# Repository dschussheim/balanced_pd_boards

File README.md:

# balanced_pd_boards
Eagle files for balance photodiode detectors

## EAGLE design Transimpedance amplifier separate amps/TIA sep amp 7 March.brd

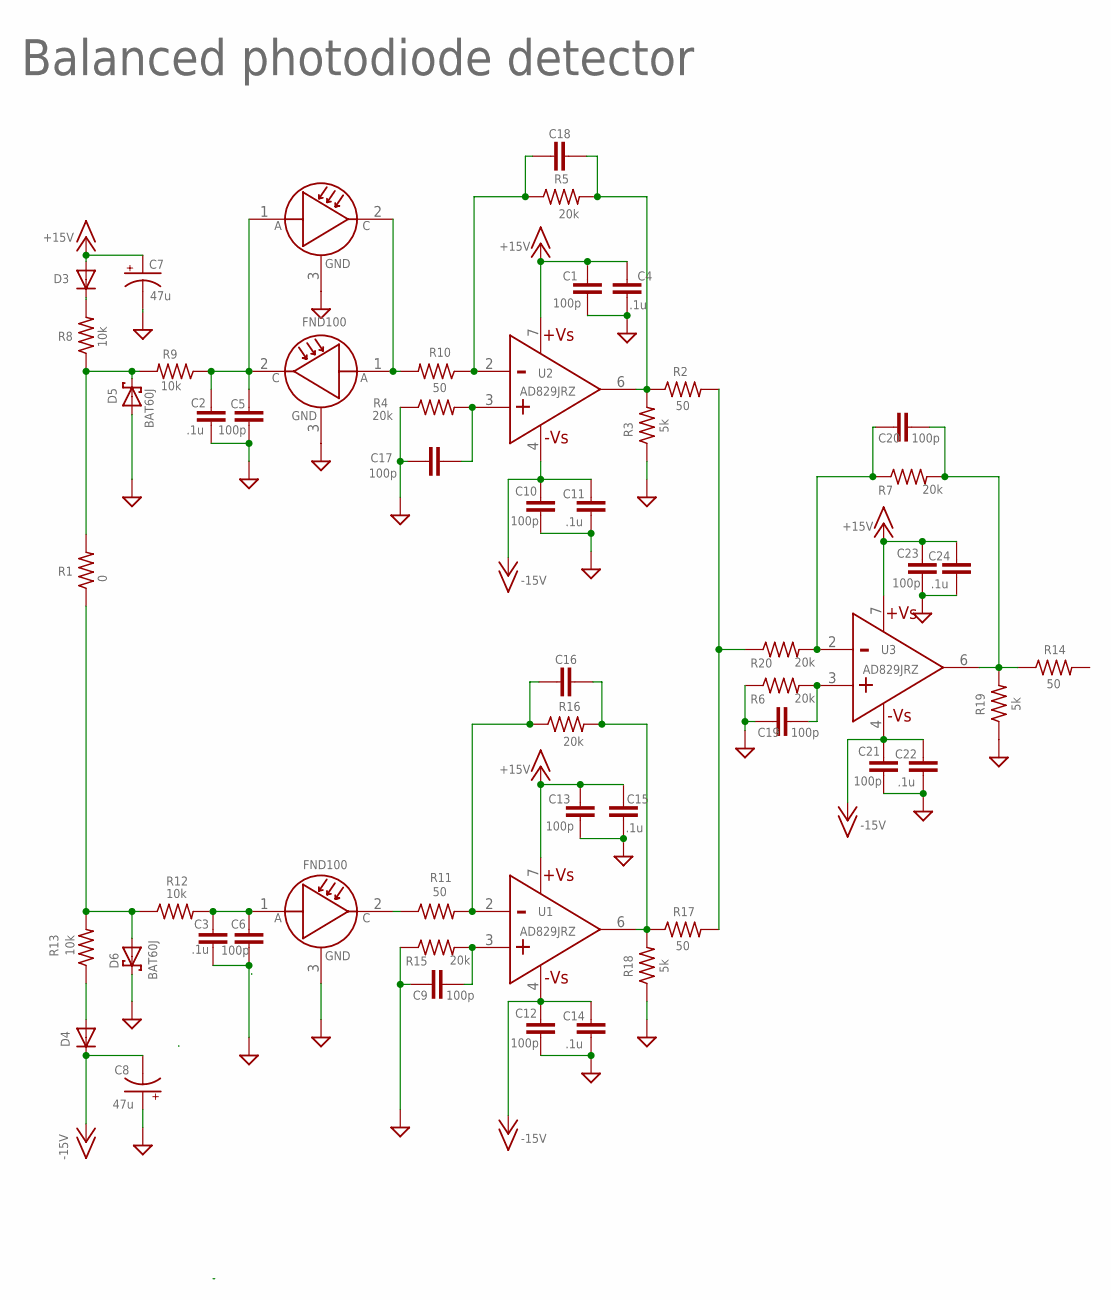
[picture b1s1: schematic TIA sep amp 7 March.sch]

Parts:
C1, C5, C6, C9, C10, C12, C13, C17, C19, C20, C21, C23: 100p; C0603
C2, C3, C4, C11, C14, C15, C22, C24: .1u; C0603
C7, C8: 47u; ETR3
C16, C18: C-EUC0603; C0603
D3, D4: SOD523DIODE; SOD523
D5, D6: BAT60J; SOD323_ST
R1: 0; R0603
R2, R10, R11, R14, R17: 50; R0603
R3, R18, R19: 5k; R0603
R4, R5, R6, R7, R15, R16, R20: 20k; R0603
R8, R9, R12, R13: 10k; R0603
U1, U2, U3: AD829JRZ; SOIC127P600X175-8N
U$1, U$2, U$4: FND100; TO254P939X470-3P

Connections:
+15V: C1.2, C4.2, C7.+, C13.2, C15.2, C23.2, C24.2, D3.A, U1.7 (+VS), U2.7 (+VS), U3.7 (+VS)
-15V: C8.-, C10.2, C11.2, C12.2, C14.2, C21.2, C22.2, D4.C, U1.4 (-VS), U2.4 (-VS), U3.4 (-VS)
GND: C1.1, C2.1, C3.1, C4.1, C5.1, C6.1, C7.-, C8.+, C9.1, C10.1, C11.1, C12.1, C13.1, C14.1, C15.1, C17.1, C19.1, C21.1, C22.1, C23.1, C24.1, D5.A, D6.C, R3.1, R4.1, R6.1, R15.1, R18.1, R19.1, U$1.3 (GND), U$2.3 (GND), U$4.3 (GND)
unnamed: D3.C, R8.2
unnamed: C16.1, R11.2, R16.1, U1.2 (-IN)
unnamed: C16.2, R16.2, R17.1, R18.2, U1.6 (OUTPUT)
unnamed: C17.2, R4.2, U2.3 (+IN)
unnamed: C2.2, C5.2, R9.1, U$1.2 (C), U$4.1 (A)
unnamed: C18.1, R5.1, R10.1, U2.2 (-IN)
unnamed: D5.C, R1.2, R8.1, R9.2
unnamed: R10.2, U$1.1 (A), U$4.2 (C)
unnamed: R11.1, U$2.2 (C)
unnamed: C3.2, C6.2, R12.2, U$2.1 (A)
unnamed: D6.A, R1.1, R12.1, R13.2
unnamed: D4.A, R13.1
unnamed: R2.2, R17.2, R20.1
unnamed: C18.2, R2.1, R3.2, R5.2, U2.6 (OUTPUT)
unnamed: C9.2, R15.2, U1.3 (+IN)
unnamed: C19.2, R6.2, U3.3 (+IN)
unnamed: C20.2, R7.2, R14.1, R19.2, U3.6 (OUTPUT)
unnamed: C20.1, R7.1, R20.2, U3.2 (-IN)

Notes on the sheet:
FND100
Balanced photodiode detector

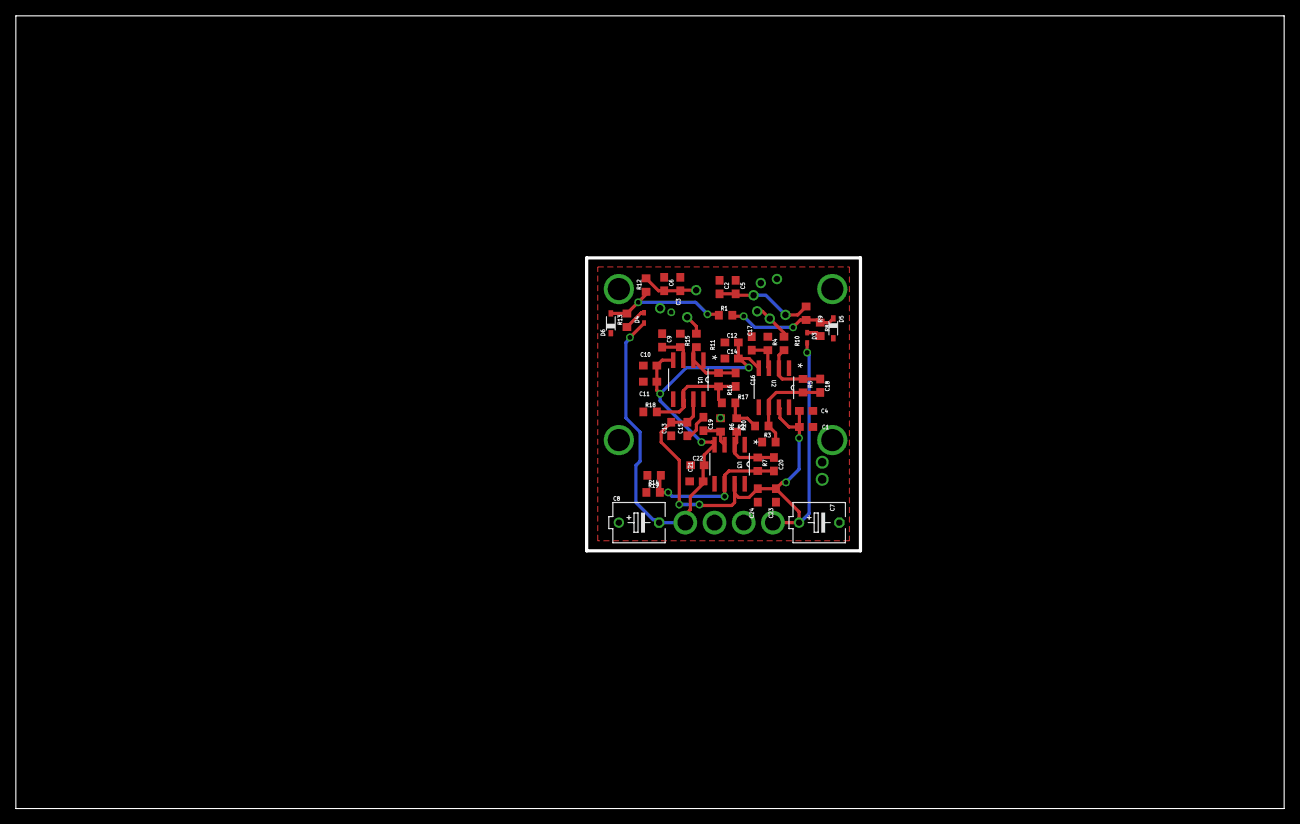
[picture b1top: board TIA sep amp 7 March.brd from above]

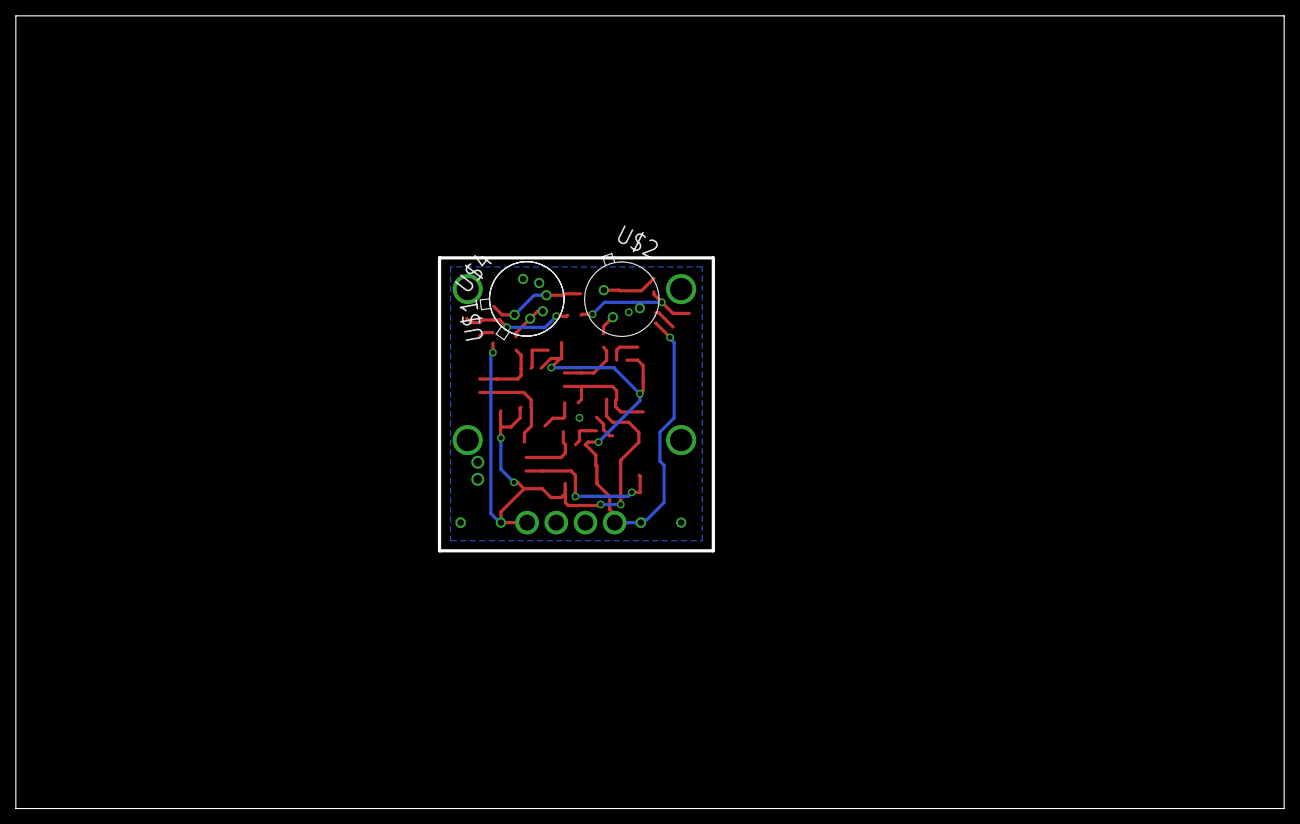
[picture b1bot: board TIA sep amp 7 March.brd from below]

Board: 2 copper layers, 159.6 x 99.6 mm, 54 parts (3 on the bottom side), 21 nets.

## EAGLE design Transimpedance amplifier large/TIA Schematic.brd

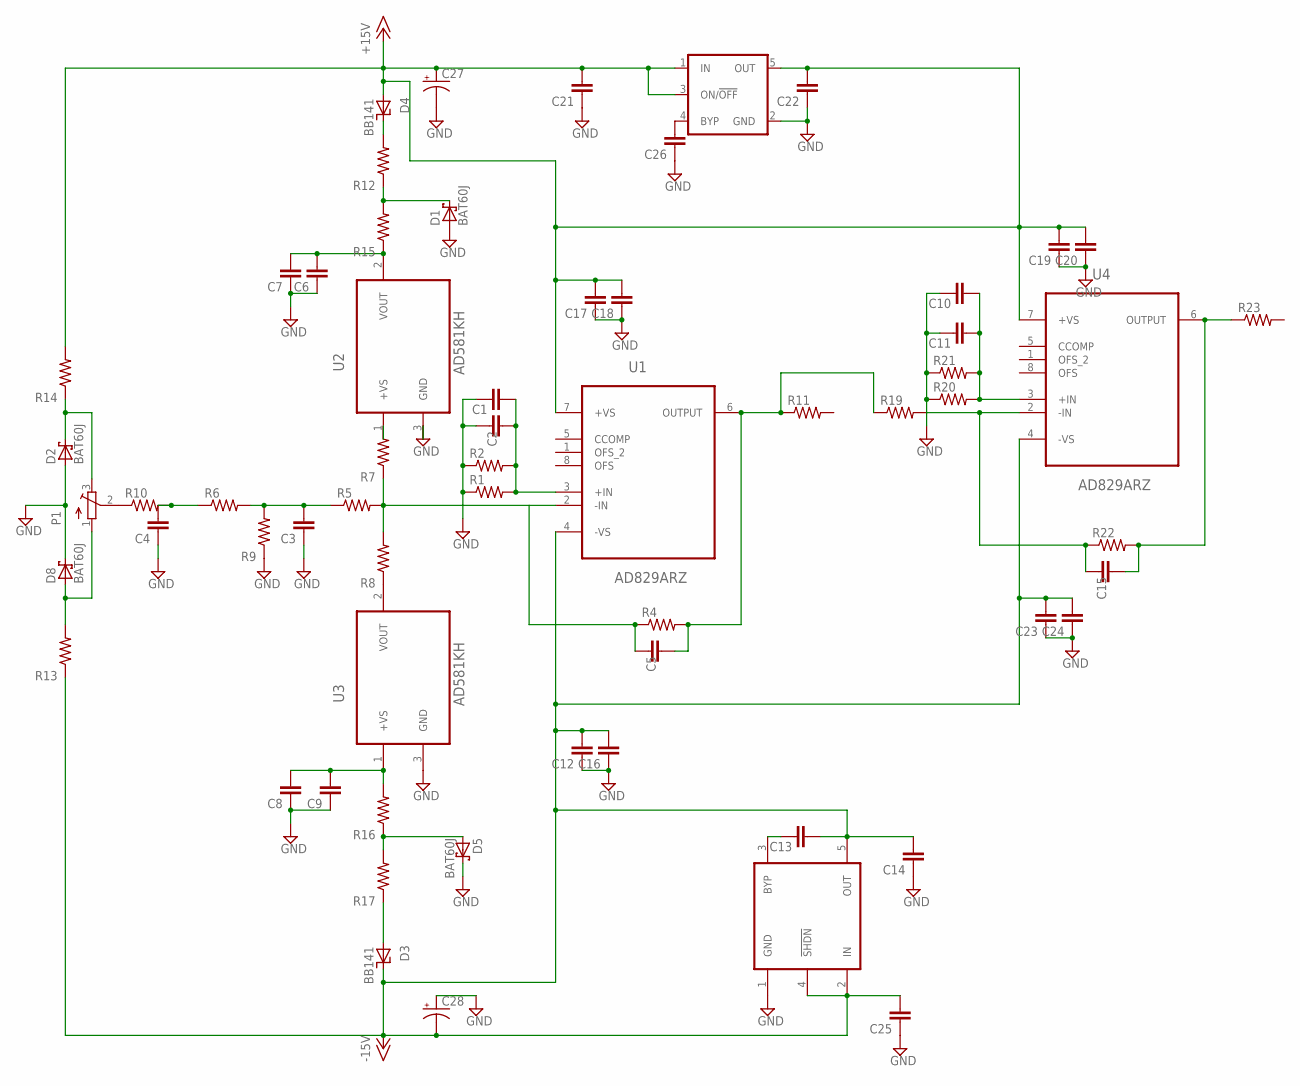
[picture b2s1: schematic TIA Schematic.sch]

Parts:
C1, C2, C3, C4, C5, C6, C7, C8, C9, C10, C11, C12, C13, C14, C15, C16, C17, C18, C19, C20, C21, C22, C23, C24, C25, C26: C-EUC0603; C0603
C27, C28: CPOL-USETR3; ETR3
D1, D2, D5, D8: BAT60J; SOD323_ST
D3, D4: BB141; SOD523
P1: TRIM_EU-3223G; 3223G
R1, R2, R4, R5, R6, R7, R8, R9, R10, R11, R12, R13, R14, R15, R16, R17, R19, R20, R21, R22, R23: R-US_R0603; R0603
U1, U4: AD829ARZ; SOIC127P600X175-8N
U2, U3: AD581KH; TO254P939X470-3P
U7: LP2992M5; SOT23-5
U8: LT1964; SOT23-5

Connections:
+15V: C17.2, C18.2, C19.2, C20.2, C21.2, C22.2, C27.+, D4.A, R14.2, U1.7 (+VS), U4.7 (+VS), U7.1 (IN), U7.3 (ON/!OFF!), U7.5 (OUT)
-15V: C12.2, C13.2, C14.2, C16.2, C23.2, C24.2, C25.2, C28.-, D3.C, R13.1, U1.4 (-VS), U4.4 (-VS), U8.2 (IN), U8.4 (!SHDN!), U8.5 (OUT)
GND: C1.1, C2.1, C3.1, C4.1, C6.1, C7.1, C8.1, C9.1, C10.1, C11.1, C12.1, C14.1, C16.1, C17.1, C18.1, C19.1, C20.1, C21.1, C22.1, C23.1, C24.1, C25.1, C26.1, C27.-, C28.+, D1.A, D2.A, D5.C, D8.C, R1.1, R2.1, R9.1, R20.1, R21.1, U2.3 (GND), U3.3 (GND), U7.2 (GND), U8.1 (GND)
unnamed: D4.C, R12.2
unnamed: P1.2 (S), R10.1
unnamed: C3.2, R5.1, R6.2, R9.2
unnamed: C4.2, R6.1, R10.2
unnamed: C1.2, C2.2, R1.2, R2.2, U1.3 (+IN)
unnamed: C5.2, R4.2, R11.1, R19.1, U1.6 (OUTPUT)
unnamed: C5.1, R4.1, R5.2, R7.1, R8.2, U1.2 (-IN)
unnamed: D1.C, R12.1, R15.2
unnamed: R7.2, U2.1 (+VS)
unnamed: R8.1, U3.2 (VOUT)
unnamed: C8.2, C9.2, R16.2, U3.1 (+VS)
unnamed: D5.A, R16.1, R17.2
unnamed: D3.A, R17.1
unnamed: D2.C, P1.3 (E), R14.1
unnamed: D8.A, P1.1 (A), R13.2
unnamed: C6.2, C7.2, R15.1, U2.2 (VOUT)
unnamed: C15.1, R19.2, R22.1, U4.2 (-IN)
unnamed: C10.2, C11.2, R20.2, R21.2, U4.3 (+IN)
unnamed: C26.2, U7.4 (BYP)
unnamed: C13.1, U8.3 (BYP)
unnamed: C15.2, R22.2, R23.1, U4.6 (OUTPUT)

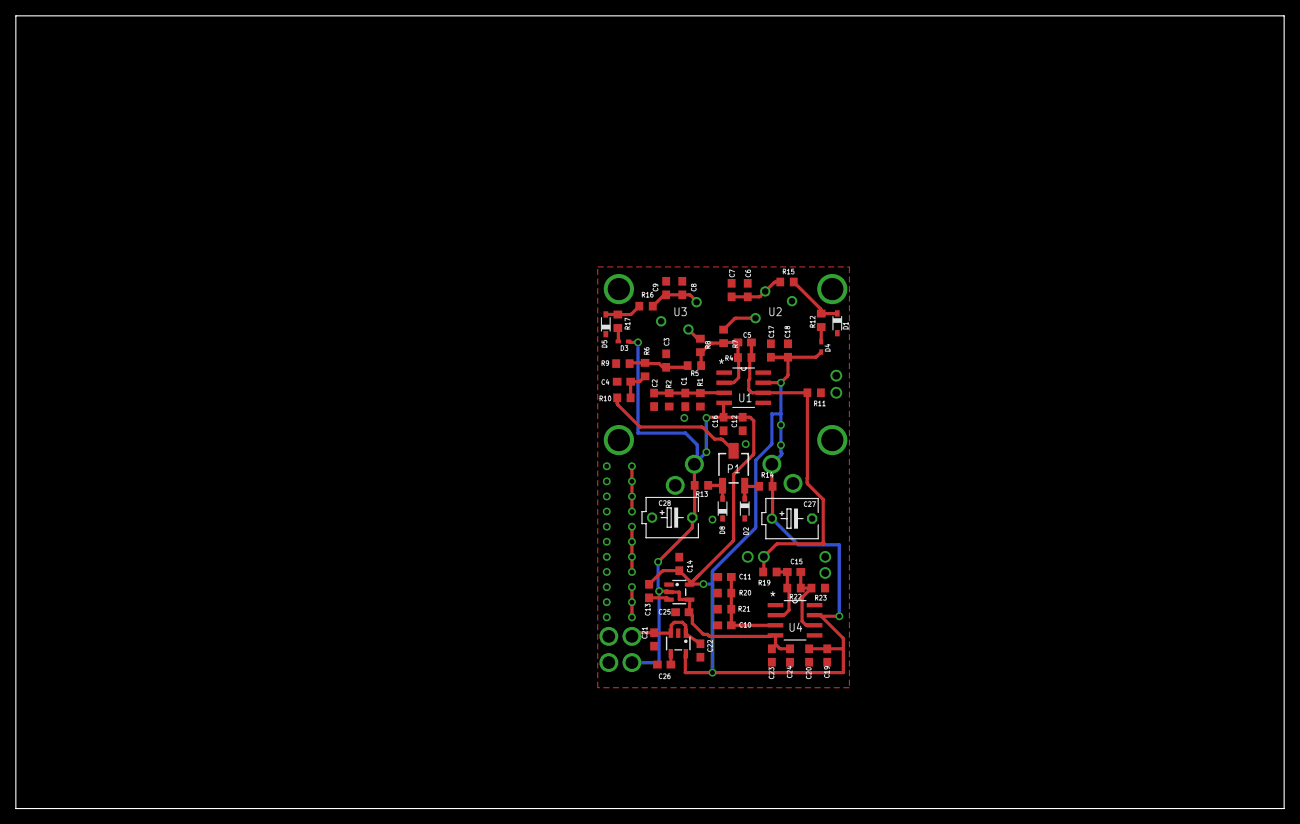
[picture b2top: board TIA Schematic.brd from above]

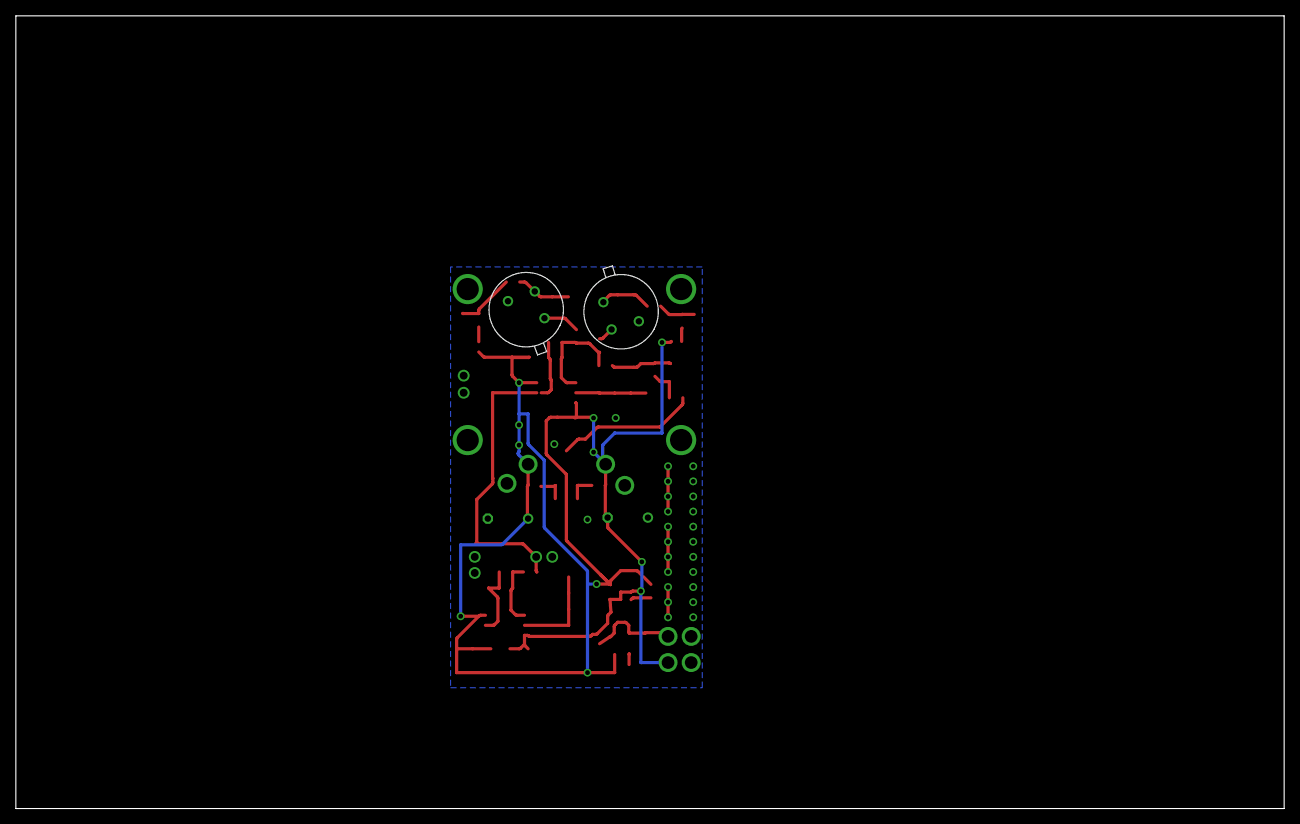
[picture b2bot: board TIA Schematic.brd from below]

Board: 2 copper layers, 160.0 x 100.0 mm, 62 parts (2 on the bottom side), 24 nets.

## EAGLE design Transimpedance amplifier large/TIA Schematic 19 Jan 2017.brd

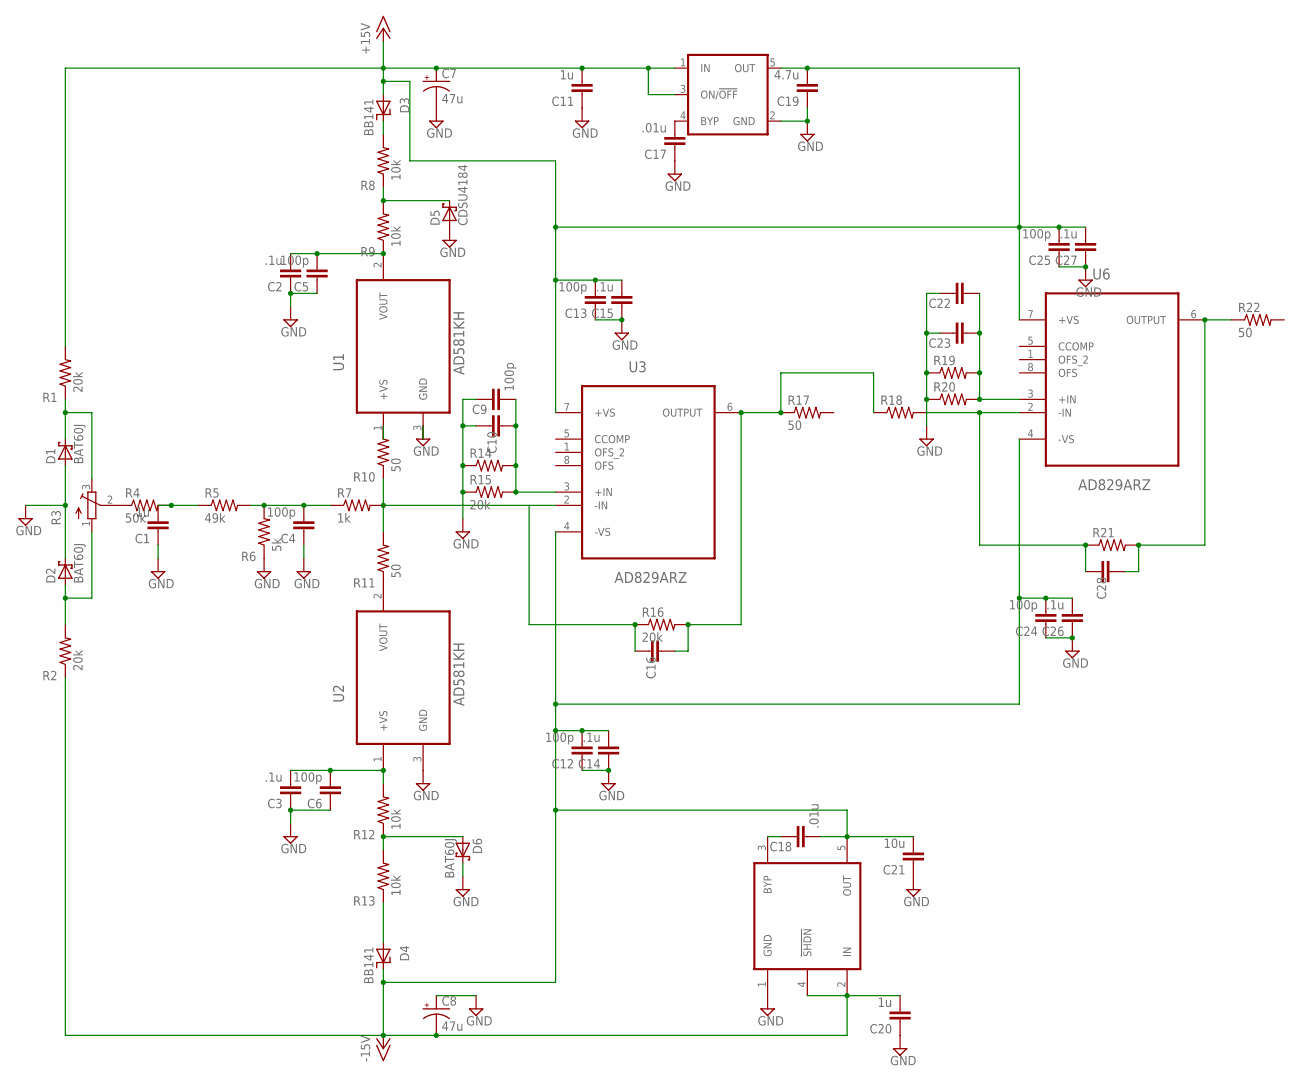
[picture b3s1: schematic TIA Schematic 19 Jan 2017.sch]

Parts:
C1, C2, C3, C14, C15, C26, C27: .1u; C0603
C4, C5, C6, C9, C12, C13, C24, C25: 100p; C0603
C7, C8: 47u; ETR3
C10, C16, C22, C23, C28: C-EUC0603; C0603
C11, C20: 1u; C0603
C17, C18: .01u; C0603
C19: 4.7u; C0603
C21: 10u; C0603
D1, D2, D6: BAT60J; SOD323_ST
D3, D4: BB141; SOD523
D5: CDSU4184; SOD323_ST
R1, R2, R15, R16: 20k; R0603
R3: TRIM_EU-3223G; 3223G
R4: 50k; R0603
R5: 49k; R0603
R6: 5k; R0603
R7: 1k; R0603
R8, R9, R12, R13: 10k; R0603
R10, R11, R17, R22: 50; R0603
R14, R18, R19, R20, R21: R-US_R0603; R0603
U1, U2: AD581KH; TO254P939X470-3P
U3, U6: AD829ARZ; SOIC127P600X175-8N
U4: LP2992M5; SOT23-5
U5: LT1964; SOT23-5

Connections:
+15V: C7.+, C11.2, C13.2, C15.2, C19.2, C25.2, C27.2, D3.A, R1.2, U3.7 (+VS), U4.1 (IN), U4.3 (ON/!OFF!), U4.5 (OUT), U6.7 (+VS)
-15V: C8.-, C12.2, C14.2, C18.2, C20.2, C21.2, C24.2, C26.2, D4.C, R2.1, U3.4 (-VS), U5.2 (IN), U5.4 (!SHDN!), U5.5 (OUT), U6.4 (-VS)
GND: C1.1, C2.1, C3.1, C4.1, C5.1, C6.1, C7.-, C8.+, C9.1, C10.1, C11.1, C12.1, C13.1, C14.1, C15.1, C17.1, C19.1, C20.1, C21.1, C22.1, C23.1, C24.1, C25.1, C26.1, C27.1, D1.A, D2.C, D5.A, D6.C, R6.1, R14.1, R15.1, R19.1, R20.1, U1.3 (GND), U2.3 (GND), U4.2 (GND), U5.1 (GND)
unnamed: D3.C, R8.2
unnamed: R3.2 (S), R4.1
unnamed: C4.2, R5.2, R6.2, R7.1
unnamed: C1.2, R4.2, R5.1
unnamed: C9.2, C10.2, R14.2, R15.2, U3.3 (+IN)
unnamed: C16.2, R16.2, R17.1, R18.1, U3.6 (OUTPUT)
unnamed: C16.1, R7.2, R10.1, R11.2, R16.1, U3.2 (-IN)
unnamed: D5.C, R8.1, R9.2
unnamed: R10.2, U1.1 (+VS)
unnamed: R11.1, U2.2 (VOUT)
unnamed: C3.2, C6.2, R12.2, U2.1 (+VS)
unnamed: D6.A, R12.1, R13.2
unnamed: D4.A, R13.1
unnamed: D1.C, R1.1, R3.3 (E)
unnamed: D2.A, R2.2, R3.1 (A)
unnamed: C2.2, C5.2, R9.1, U1.2 (VOUT)
unnamed: C28.1, R18.2, R21.1, U6.2 (-IN)
unnamed: C22.2, C23.2, R19.2, R20.2, U6.3 (+IN)
unnamed: C17.2, U4.4 (BYP)
unnamed: C18.1, U5.3 (BYP)
unnamed: C28.2, R21.2, R22.1, U6.6 (OUTPUT)

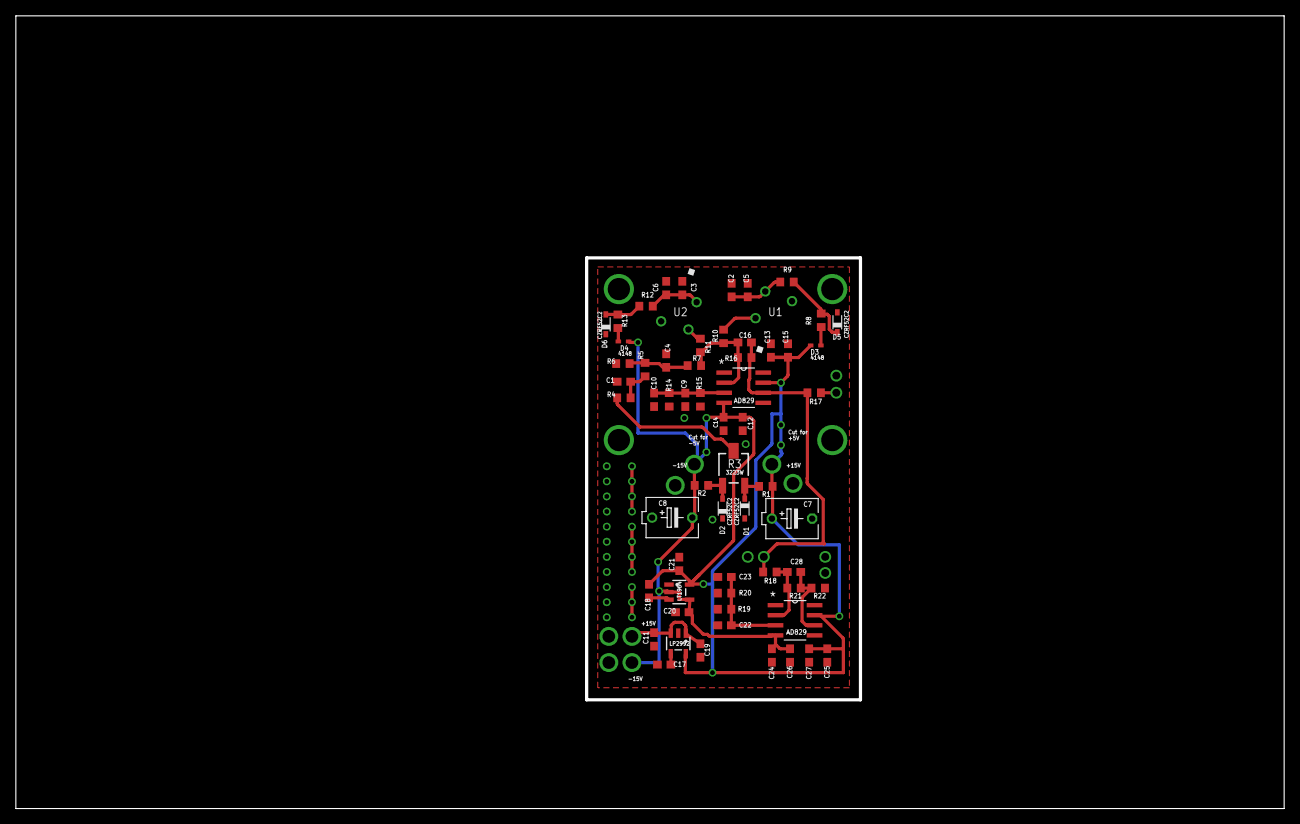
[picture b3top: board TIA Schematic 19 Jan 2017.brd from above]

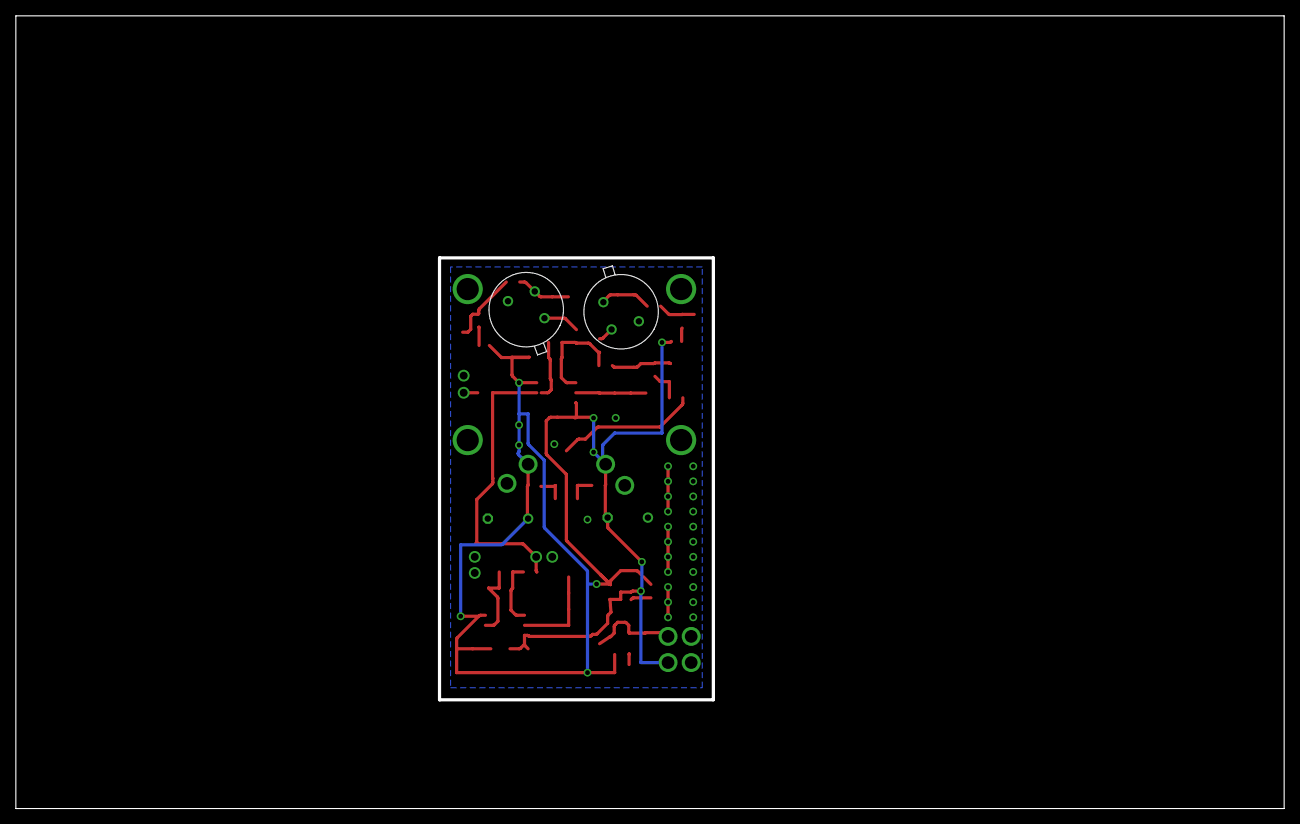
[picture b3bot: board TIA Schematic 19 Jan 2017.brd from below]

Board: 2 copper layers, 159.6 x 99.6 mm, 62 parts (2 on the bottom side), 24 nets.

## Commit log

2017-05-30 30 May 2017
    Commit of large board (extra amps), small board (one amp for both currents), and separate amp (each current gets its own amplifier) versions of balanced transimpedance amplifier boards.
